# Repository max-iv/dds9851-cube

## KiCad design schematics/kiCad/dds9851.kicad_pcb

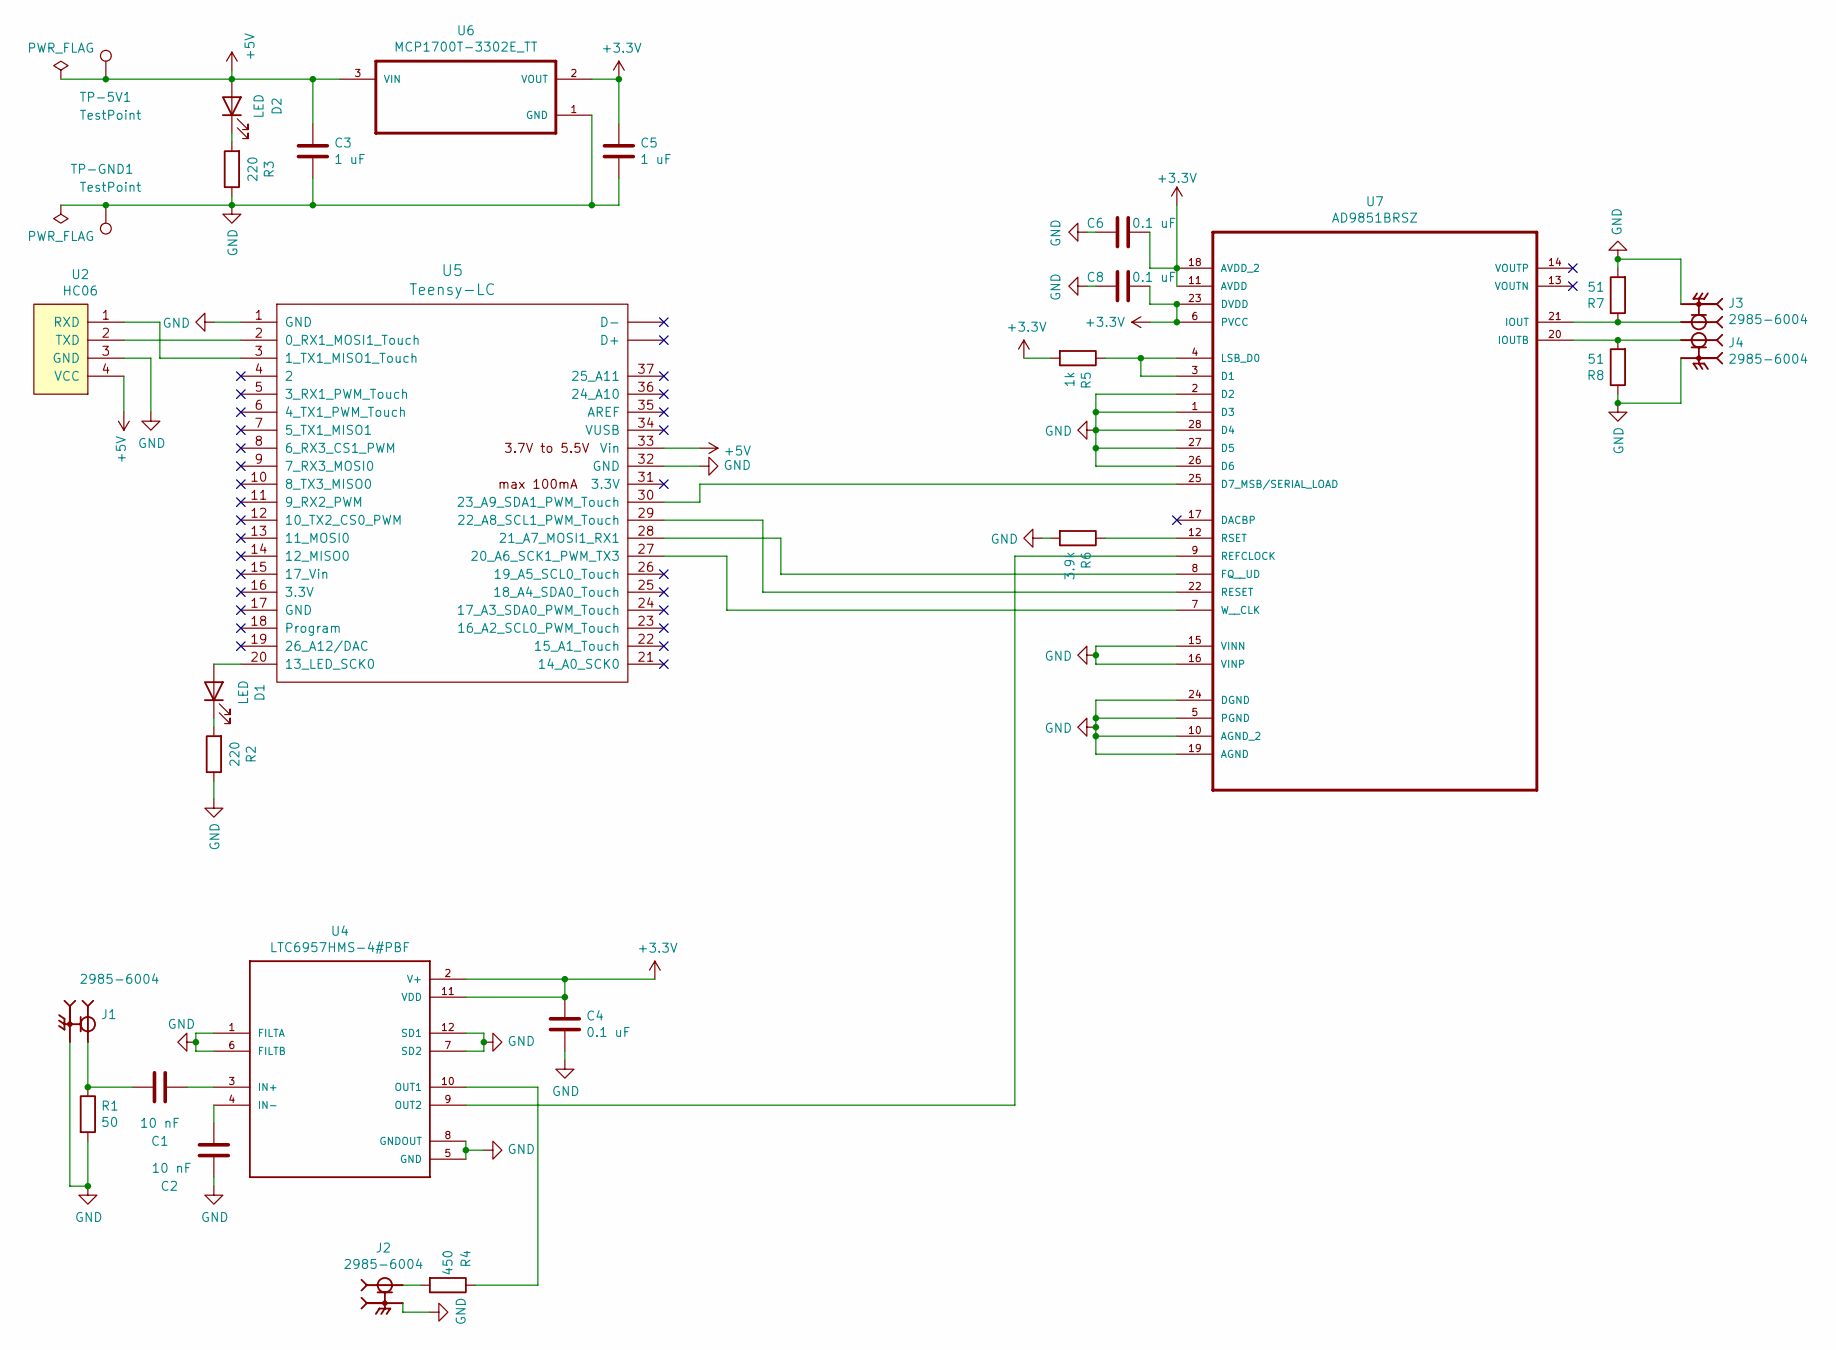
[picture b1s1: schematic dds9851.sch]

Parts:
C1, C2: 10 nF; C_1206_3216Metric_Pad1.42x1.75mm_HandSolder
C3, C5: 1 uF; C_1206_3216Metric_Pad1.42x1.75mm_HandSolder
C4, C6, C8: 0.1 uF; C_1206_3216Metric_Pad1.42x1.75mm_HandSolder
D1, D2: LED; LED_D5.0mm
J1, J2, J3, J4: 2985-6004; AMPHENOL_2985-6004
R1: 50; R_1206_3216Metric_Pad1.42x1.75mm_HandSolder
R2, R3: 220; R_1206_3216Metric_Pad1.42x1.75mm_HandSolder
R4: 450; R_1206_3216Metric_Pad1.42x1.75mm_HandSolder
R5: 1k; R_1206_3216Metric_Pad1.42x1.75mm_HandSolder
R6: 3.9k; R_1206_3216Metric_Pad1.42x1.75mm_HandSolder
R7, R8: 51; R_1206_3216Metric_Pad1.42x1.75mm_HandSolder
TP-5V1: TestPoint; PinHeader_1x01_P2.54mm_Vertical
TP-GND1: TestPoint; PinHeader_1x01_P2.54mm_Vertical
U2: HC06
U4: LTC6957HMS-4#PBF; SOP65P490X110-12N
U5: Teensy-LC; Teensy30_31_32_LC
U6: MCP1700T-3302E_TT; SOT95P237X112-3N
U7: AD9851BRSZ; SOP65P780X200-28N

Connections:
+3V3: C4.1, C5.1, C6.2, C8.2, R5.2, U4.2 (V+), U4.11 (VDD), U6.2 (VOUT), U7.6 (PVCC), U7.11 (AVDD), U7.18 (AVDD_2), U7.23 (DVDD)
+5V: C3.1, D2.2 (A), TP-5V1.1, U2.4 (VCC), U5.33 (Vin), U6.3 (VIN)
GND: C2.2, C3.2, C4.2, C5.2, C6.1, C8.1, J1.S1, J1.S2, J1.S3, J1.S4, J2.S1, J2.S2, J2.S3, J2.S4, J3.S1, J3.S2, J3.S3, J3.S4, J4.S1, J4.S2, J4.S3, J4.S4, R1.2, R2.1, R3.1, R6.2, R7.2, R8.1, TP-GND1.1, U2.3 (GND), U4.1 (FILTA), U4.5 (GND), U4.6 (FILTB), U4.7 (SD2), U4.8 (GNDOUT), U4.12 (SD1), U5.1 (GND), U5.32 (GND), U6.1 (GND), U7.1 (D3), U7.2 (D2), U7.5 (PGND), U7.10 (AGND_2), U7.15 (VINN), U7.16 (VINP), U7.19 (AGND), U7.24 (DGND), U7.26 (D6), U7.27 (D5), U7.28 (D4)
unnamed: C1.1, U4.3 (IN+)
unnamed: C1.2, J1.1, R1.1
unnamed: C2.1, U4.4 (IN-)
unnamed: D1.1 (K), R2.2
unnamed: D1.2 (A), U5.20 (13_LED_SCK0)
unnamed: D2.1 (K), R3.2
unnamed: J2.1, R4.2
unnamed: J3.1, R7.1, U7.21 (IOUT)
unnamed: J4.1, R8.2, U7.20 (IOUTB)
unnamed: R4.1, U4.10 (OUT1)
unnamed: R5.1, U7.3 (D1), U7.4 (LSB_D0)
unnamed: R6.1, U7.12 (RSET)
unnamed: U2.1 (RXD), U5.3 (1_TX1_MISO1_Touch)
unnamed: U2.2 (TXD), U5.2 (0_RX1_MOSI1_Touch)
unnamed: U4.9 (OUT2), U7.9 (REFCLOCK)
unnamed: U5.27 (20_A6_SCK1_PWM_TX3), U7.7 (W__CLK)
unnamed: U5.28 (21_A7_MOSI1_RX1), U7.8 (FQ__UD)
unnamed: U5.29 (22_A8_SCL1_PWM_Touch), U7.22 (RESET)
unnamed: U5.30 (23_A9_SDA1_PWM_Touch), U7.25 (D7_MSB/SERIAL_LOAD)

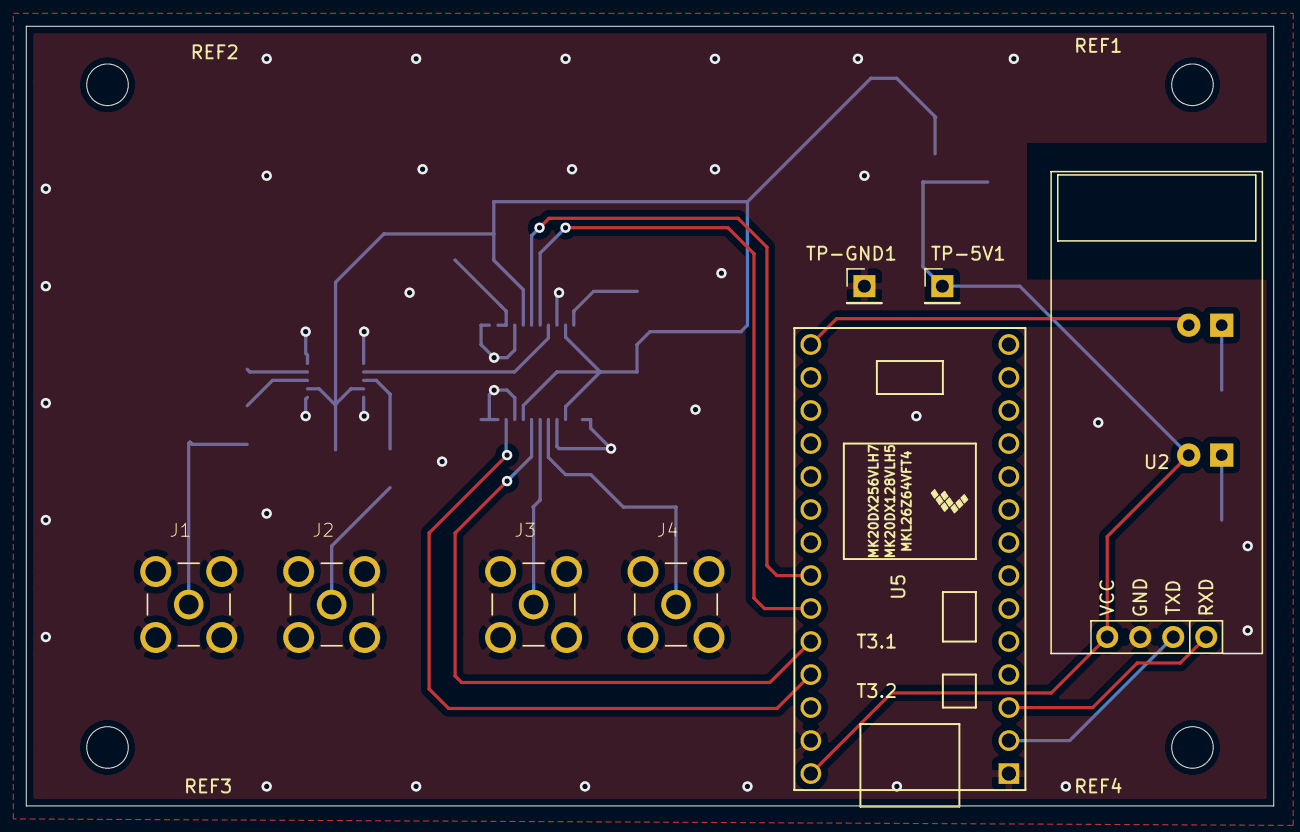
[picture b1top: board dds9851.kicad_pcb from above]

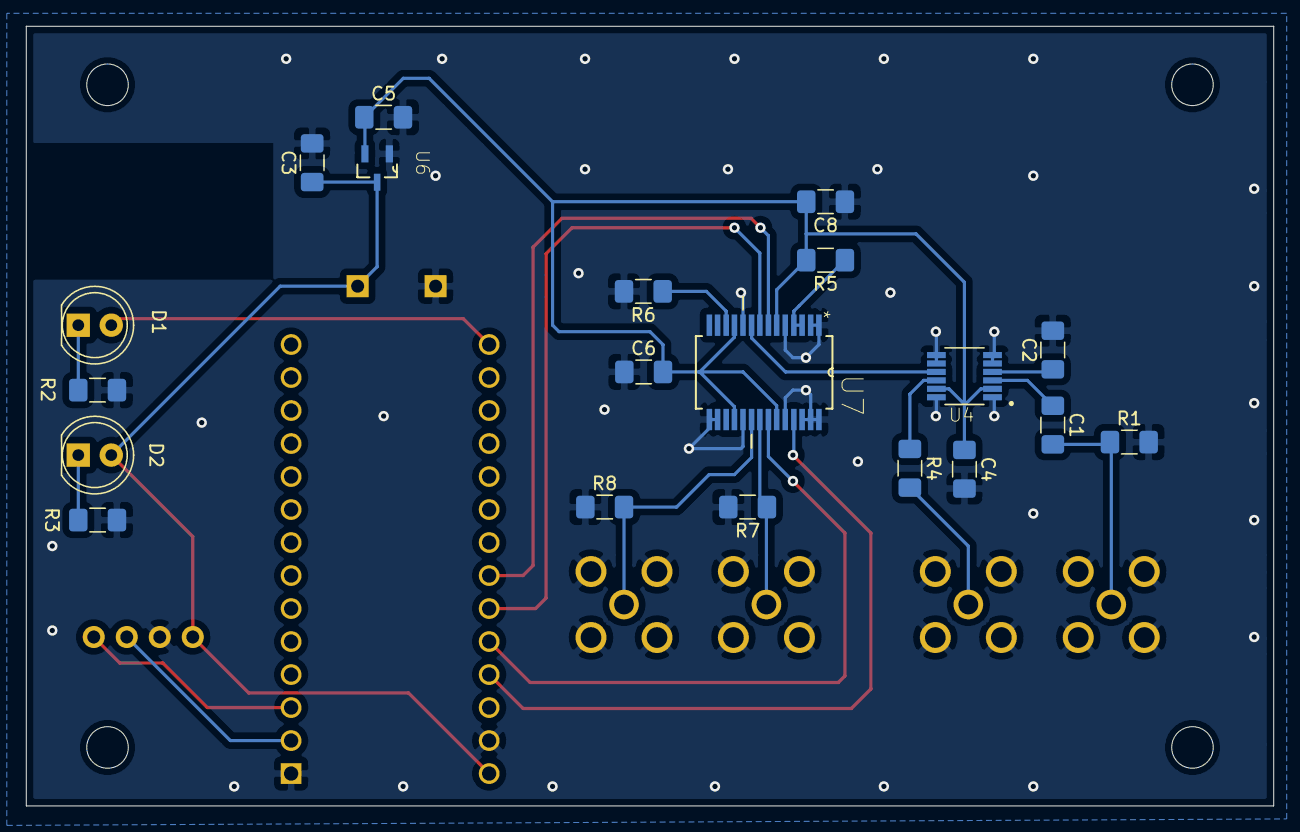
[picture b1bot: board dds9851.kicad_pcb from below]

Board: 2 copper layers, 96.0 x 60.0 mm, 32 parts (20 on the bottom side), 22 nets.

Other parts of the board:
REF1, REF2, REF3, REF4: MountingHole_3.2mm_M3

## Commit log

2020-02-25 added kicad schem
2020-02-29 changed serial handshake
2020-03-09 forked from basic
2020-03-10 binary transfer working
2020-03-11 changed buffer to 64 bytes
2020-03-12 got handshake with tray working
2020-03-12 modular code
2020-03-15 working with tray
2020-03-16 changed init cond
2020-03-20 change init LEDS
2020-09-03 cloned from basic-cube
2020-10-06 new schematic
2020-10-06 cleanup libraries
2020-10-06 added 9851 LTC, and MCP libraries
2020-10-09 schematic done - working on pcb
2020-10-12 components placed
2020-10-13 pcb ready
